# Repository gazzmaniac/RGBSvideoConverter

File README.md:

# RGBSvideoConverter
RGB to SVideo converter for Amiga computers

Comments May 2024
----------------------------------------------------
This project works fine, it's an easy way to get SVideo from your Amiga.
Be aware there are no buffers between the Amiga and video encoder.  This is a point of failure and I know of one video encoder that has failed because of it.  
In an ideal world I'd update it to have a video amplifier in between to protect both the Amiga and the encoder but with other open source alternatives (especially RGB2HDMI) now available there is very little point pursuing further development.  It may be of use for someone to incorporate into other projects.
If you do use this in a derivative project please give credit and make it open source.
Note the new license

Readme
----------------------------------------------------
Licensed under the CERN Open Hardware Licence Version 2 - Strongly Reciprocal (https://ohwr.org/)
Please be aware that some of the footprints may not be open source even though they are public domain.

This device is based around the AD723ARUZ PAL encoder.  It converts 15 kHz RGB signal to SVideo and Composite.  It is designed for and tested with the Amiga series of computers however it should work with other machines that output a 15 kHz RGB signal.  The circuit is substantially based on the examples given in the AD732ARUZ data sheet.

The video input is via a D9 socket with the same pinout as the Commodore 1084 monitor (except csync is not used) and power is 3.3-5v into a 5 mm DC power socket.  Power may be supplied from the Amiga.  A suitable cable would be:
AmigaD23 AdapterD9  AdapterPower   Signal
  16-20    1,2         sleeve       GND
    3       3                       Red
    4       4                       Green
    5       5                       Blue
    11      8                       HSync
    12      9                       VSync
    23                  pin         +5V

This project has been built and tested however no warranty is given.

Notes:
JP1 selects whether or not the YTrap filter is used.  There is no need to remove this.

Rev 1.1:
First open source release.
The only changes are in the silkscreens to reflect the now open nature of the project.

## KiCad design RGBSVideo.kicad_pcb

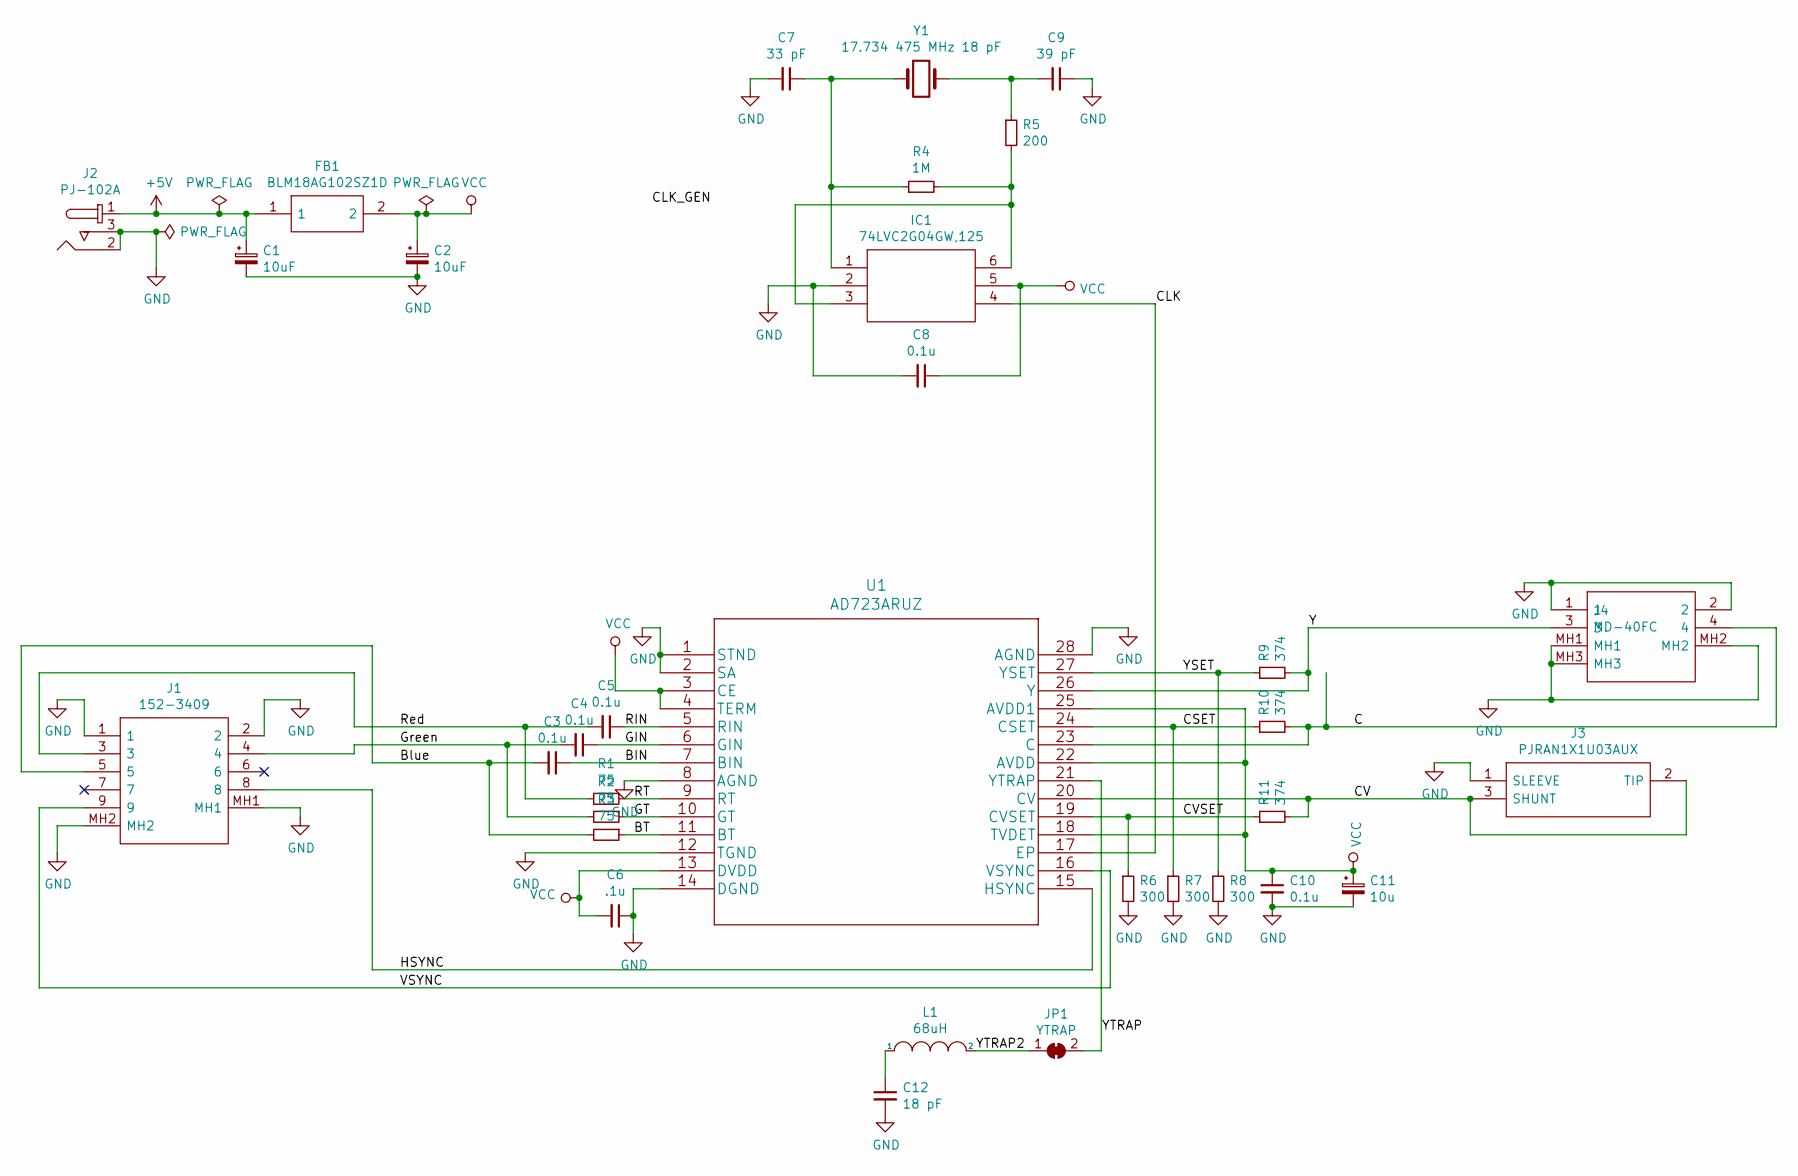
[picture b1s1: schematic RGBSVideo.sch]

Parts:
C1, C2: 10uF; C_0805_2012Metric_Pad1.15x1.40mm_HandSolder
C3, C4, C5, C8, C10: 0.1u; C_0805_2012Metric_Pad1.15x1.40mm_HandSolder
C6: .1u; C_0805_2012Metric_Pad1.15x1.40mm_HandSolder
C7: 33 pF; C_0805_2012Metric_Pad1.15x1.40mm_HandSolder
C9: 39 pF; C_0805_2012Metric_Pad1.15x1.40mm_HandSolder
C11: 10u; C_0805_2012Metric_Pad1.15x1.40mm_HandSolder
C12: 18 pF; C_0805_2012Metric_Pad1.15x1.40mm_HandSolder
FB1: BLM18AG102SZ1D; BEADC1608X95N; Mouser Part Number 81-BLM18AG102SZ1D
IC1: 74LVC2G04GW,125; SOT65P210X110-6N; Manufacturer_Part_Number 74LVC2G04GW,125; Mouser Part Number 771-74LVC2G04GW-G
J1: 152-3409; 1523409; Mouser Part Number 152-3409
J2: PJ-102A; CUI_PJ-102A; MPN PJ-102A; Digi-Key_PN CP-102A-ND
J3: PJRAN1X1U03AUX; Mouser Part Number 502-PJRAN1X1U03AUX
J4: MD-40FC; CUI_MD-40FC
JP1: YTRAP; SolderJumper-2_P1.3mm_Bridged_RoundedPad1.0x1.5mm
L1: 68uH; L_0805_2012Metric_Pad1.15x1.40mm_HandSolder
R1, R2, R3: 75; R_0805_2012Metric_Pad1.15x1.40mm_HandSolder
R4: 1M; R_0805_2012Metric_Pad1.15x1.40mm_HandSolder
R5: 200; R_0805_2012Metric_Pad1.15x1.40mm_HandSolder
R6, R7, R8: 300; R_0805_2012Metric_Pad1.15x1.40mm_HandSolder
R9, R10, R11: 374; R_0805_2012Metric_Pad1.15x1.40mm_HandSolder
U1: AD723ARUZ
Y1: 17.734 475 MHz 18 pF; Crystal_SMD_HC49-SD_HandSoldering

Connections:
+5V: C1.1, FB1.1, J2.1
/BIN: C3.1, U1.7 (BIN)
/BT: R3.1, U1.11 (BT)
/Blue: C3.2, J1.5, R3.2
/C: J4.4, R10.2, U1.23 (C)
/CLK: IC1.4, U1.17 (EP)
/CSET: R7.1, R10.1, U1.24 (CSET)
/CV: J3.2 (TIP), J3.3 (SHUNT), R11.2, U1.20 (CV)
/CVSET: R6.1, R11.1, U1.19 (CVSET)
/GIN: C4.1, U1.6 (GIN)
/GT: R2.1, U1.10 (GT)
/Green: C4.2, J1.4, R2.2
/HSYNC: J1.8, U1.15 (HSYNC)
/RIN: C5.1, U1.5 (RIN)
/RT: R1.1, U1.9 (RT)
/Red: C5.2, J1.3, R1.2
/VSYNC: J1.9, U1.16 (VSYNC)
/Y: J4.3, R9.2, U1.26 (Y)
/YSET: R8.1, R9.1, U1.27 (YSET)
/YTRAP: JP1.2 (B), U1.21 (YTRAP)
/YTRAP2: JP1.1 (A), L1.2
GND: C1.2, C2.2, C6.1, C7.2, C8.2, C9.1, C10.2, C11.2, C12.2, IC1.2, J1.1, J1.2, J1.MH1, J1.MH2, J2.2, J2.3, J3.1 (SLEEVE), J4.1, J4.2, J4.MH1, J4.MH2, J4.MH3, R6.2, R7.2, R8.2, U1.1 (STND), U1.2 (SA), U1.8 (AGND), U1.12 (TGND), U1.14 (DGND), U1.28 (AGND)
unnamed 22: C7.1, IC1.1, R4.1, Y1.1; also elsewhere on the board
unnamed 23: C9.2, R5.1, Y1.2; also elsewhere on the board
unnamed: C12.1, L1.1
unnamed: IC1.3, IC1.6, R4.2, R5.2
VCC: C2.1, C6.2, C8.1, C10.1, C11.1, FB1.2, IC1.5, U1.3 (CE), U1.4 (TERM), U1.13 (DVDD), U1.18 (TVDET), U1.22 (AVDD), U1.25 (AVDD1)

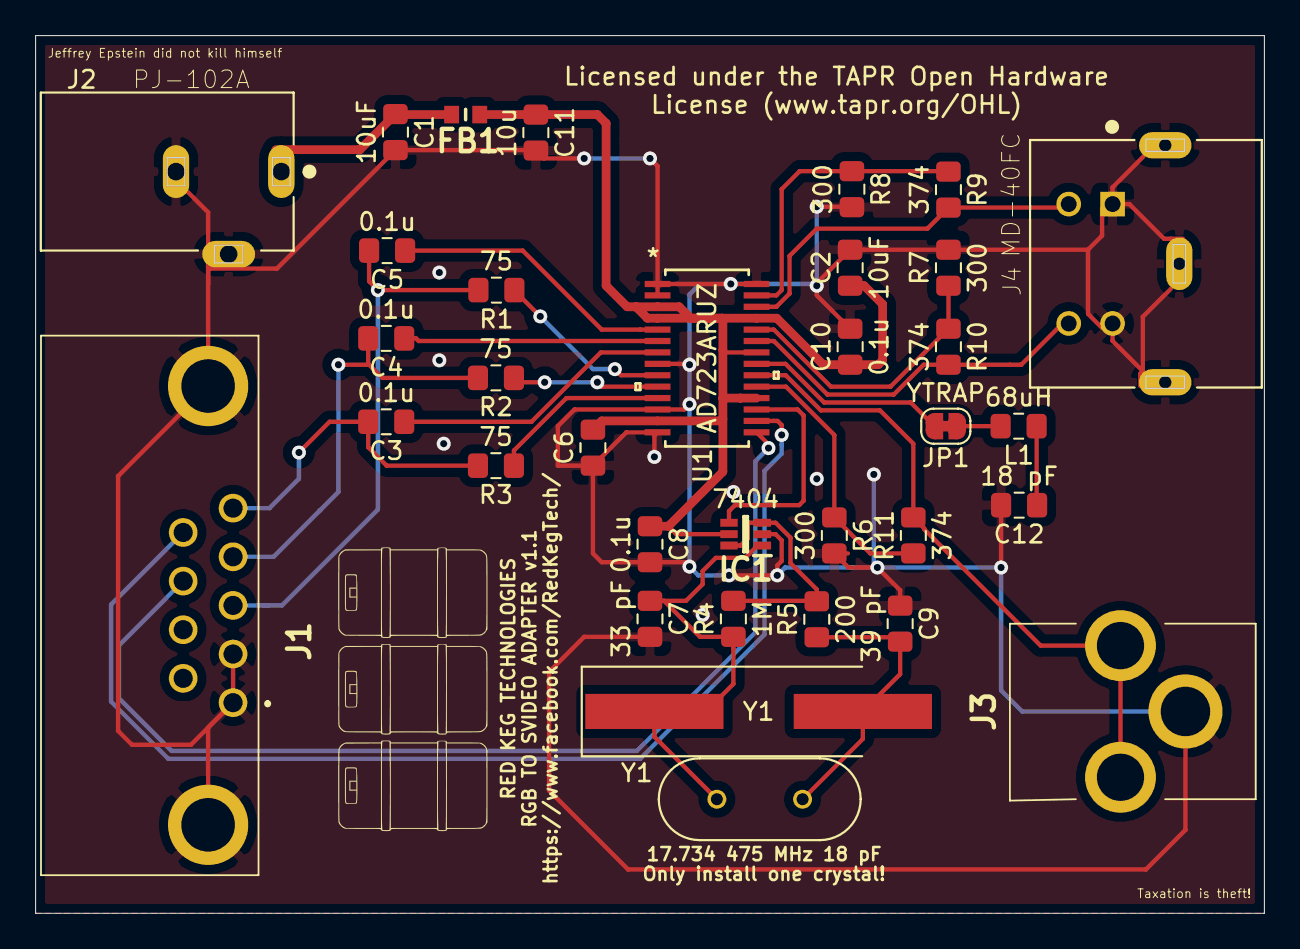
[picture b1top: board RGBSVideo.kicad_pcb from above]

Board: 2 copper layers, 70.0 x 50.0 mm, 34 parts (0 on the bottom side), 27 nets.

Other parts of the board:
XTAL_HC49P488W43L1150T466H350: VAL**; XTAL_HC49P488W43L1150T466H350

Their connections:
unnamed 22: XTAL_HC49P488W43L1150T466H350.1; also elsewhere on the board
unnamed 23: XTAL_HC49P488W43L1150T466H350.2; also elsewhere on the board

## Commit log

2024-05-17 Update LICENSE.txt
    Change to CERN Open Hardware Licence Version 2 - Strongly Reciprocal
2024-05-17 Update README.md
    Added Comments May 2024 section

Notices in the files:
RGBSVideo.kicad_pcb:
Licensed under the TAPR Open Hardware
Licensed under the TAPR Open Hardware License (www.tapr.org/OHL)
parts and their libraries:
Copyright 2016 Accelerated Designs. All rights reserved.
